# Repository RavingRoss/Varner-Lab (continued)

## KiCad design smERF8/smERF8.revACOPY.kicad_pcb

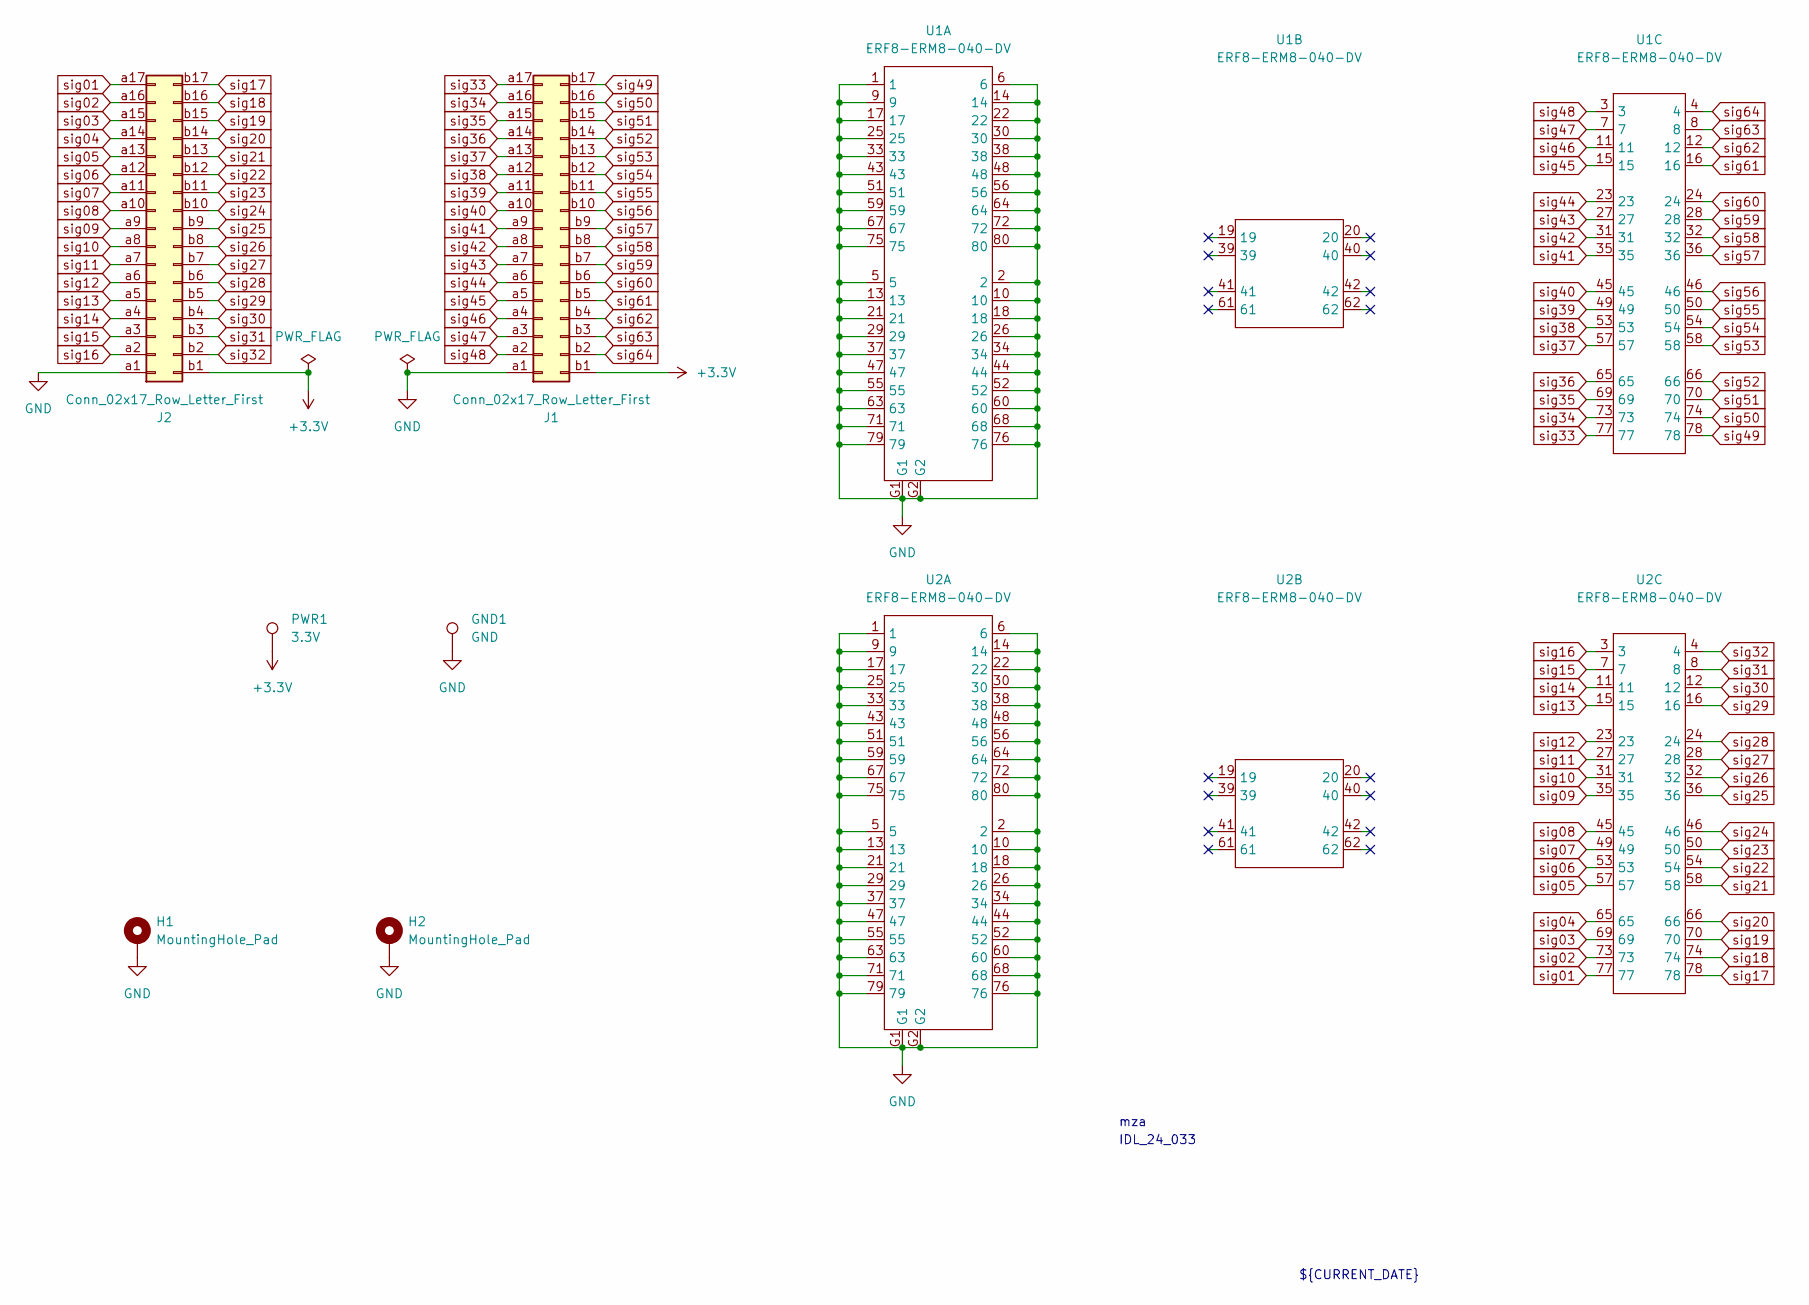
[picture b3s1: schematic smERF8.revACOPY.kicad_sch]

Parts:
GND1: GND; TestPoint_16AWG
H1, H2: MountingHole_Pad; MountingHole_2.7mm_M2.5_Pad
J1, J2: Conn_02x17_Row_Letter_First; 2x17
PWR1: 3.3V; TestPoint_16AWG
U1, U2: ERF8-ERM8-040-DV; erf8-040-dv

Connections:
+3.3V: J1.b1, J2.b1, PWR1.1
GND: GND1.1, H1.1, H2.1, J1.a1, J2.a1, U1.1, U1.2, U1.5, U1.6, U1.9, U1.10, U1.13, U1.14, U1.17, U1.18, U1.21, U1.22, U1.25, U1.26, U1.29, U1.30, U1.33, U1.34, U1.37, U1.38, U1.43, U1.44, U1.47, U1.48, U1.51, U1.52, U1.55, U1.56, U1.59, U1.60, U1.63, U1.64, U1.67, U1.68, U1.71, U1.72, U1.75, U1.76, U1.79, U1.80, U1.G1, U1.G2, U2.1, U2.2, U2.5, U2.6, U2.9, U2.10, U2.13, U2.14, U2.17, U2.18, U2.21, U2.22, U2.25, U2.26, U2.29, U2.30, U2.33, U2.34, U2.37, U2.38, U2.43, U2.44, U2.47, U2.48, U2.51, U2.52, U2.55, U2.56, U2.59, U2.60, U2.63, U2.64, U2.67, U2.68, U2.71, U2.72, U2.75, U2.76, U2.79, U2.80, U2.G1, U2.G2
sig01: J2.a17, U2.77
sig02: J2.a16, U2.73
sig03: J2.a15, U2.69
sig04: J2.a14, U2.65
sig05: J2.a13, U2.57
sig06: J2.a12, U2.53
sig07: J2.a11, U2.49
sig08: J2.a10, U2.45
sig09: J2.a9, U2.35
sig10: J2.a8, U2.31
sig11: J2.a7, U2.27
sig12: J2.a6, U2.23
sig13: J2.a5, U2.15
sig14: J2.a4, U2.11
sig15: J2.a3, U2.7
sig16: J2.a2, U2.3
sig17: J2.b17, U2.78
sig18: J2.b16, U2.74
sig19: J2.b15, U2.70
sig20: J2.b14, U2.66
sig21: J2.b13, U2.58
sig22: J2.b12, U2.54
sig23: J2.b11, U2.50
sig24: J2.b10, U2.46
sig25: J2.b9, U2.36
sig26: J2.b8, U2.32
sig27: J2.b7, U2.28
sig28: J2.b6, U2.24
sig29: J2.b5, U2.16
sig30: J2.b4, U2.12
sig31: J2.b3, U2.8
sig32: J2.b2, U2.4
sig33: J1.a17, U1.77
sig34: J1.a16, U1.73
sig35: J1.a15, U1.69
sig36: J1.a14, U1.65
sig37: J1.a13, U1.57
sig38: J1.a12, U1.53
sig39: J1.a11, U1.49
sig40: J1.a10, U1.45
sig41: J1.a9, U1.35
sig42: J1.a8, U1.31
sig43: J1.a7, U1.27
sig44: J1.a6, U1.23
sig45: J1.a5, U1.15
sig46: J1.a4, U1.11
sig47: J1.a3, U1.7
sig48: J1.a2, U1.3
sig49: J1.b17, U1.78
sig50: J1.b16, U1.74
sig51: J1.b15, U1.70
sig52: J1.b14, U1.66
sig53: J1.b13, U1.58
sig54: J1.b12, U1.54
sig55: J1.b11, U1.50
sig56: J1.b10, U1.46
sig57: J1.b9, U1.36
sig58: J1.b8, U1.32
sig59: J1.b7, U1.28
sig60: J1.b6, U1.24
sig61: J1.b5, U1.16
sig62: J1.b4, U1.12
sig63: J1.b3, U1.8
sig64: J1.b2, U1.4

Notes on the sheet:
mza
IDL_24_033
${CURRENT_DATE}

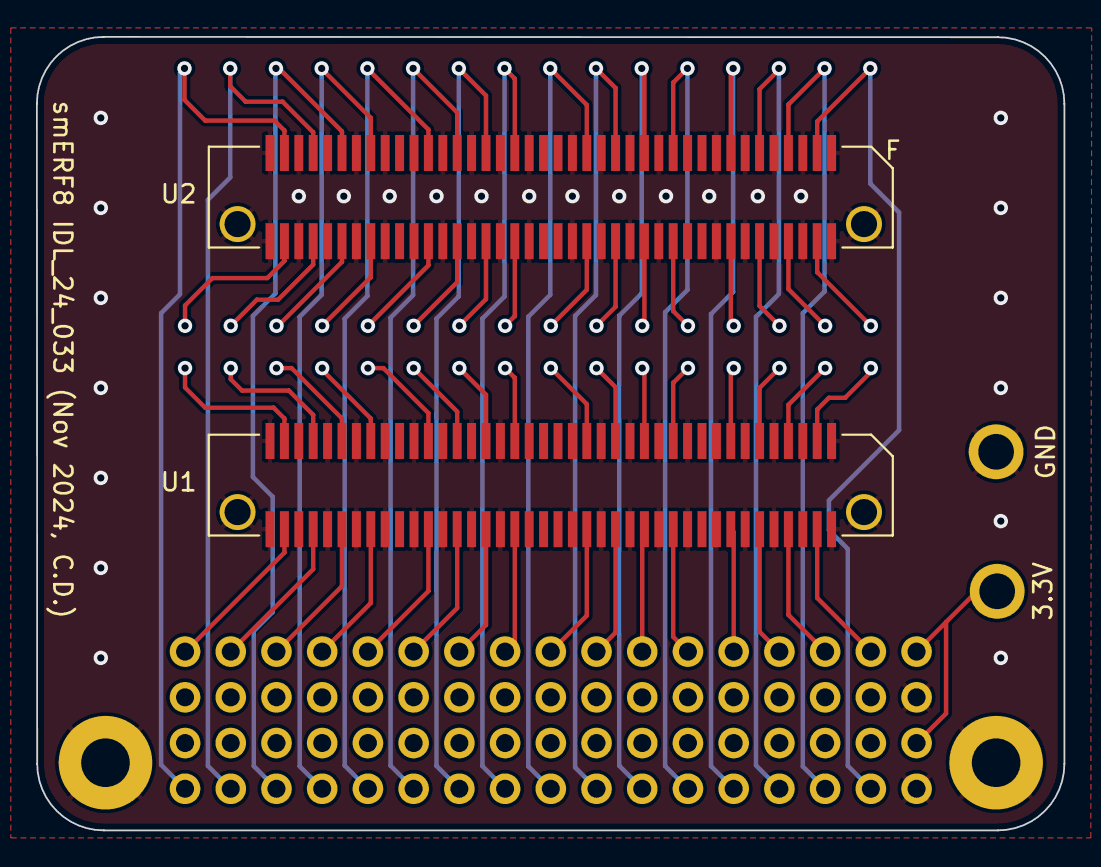
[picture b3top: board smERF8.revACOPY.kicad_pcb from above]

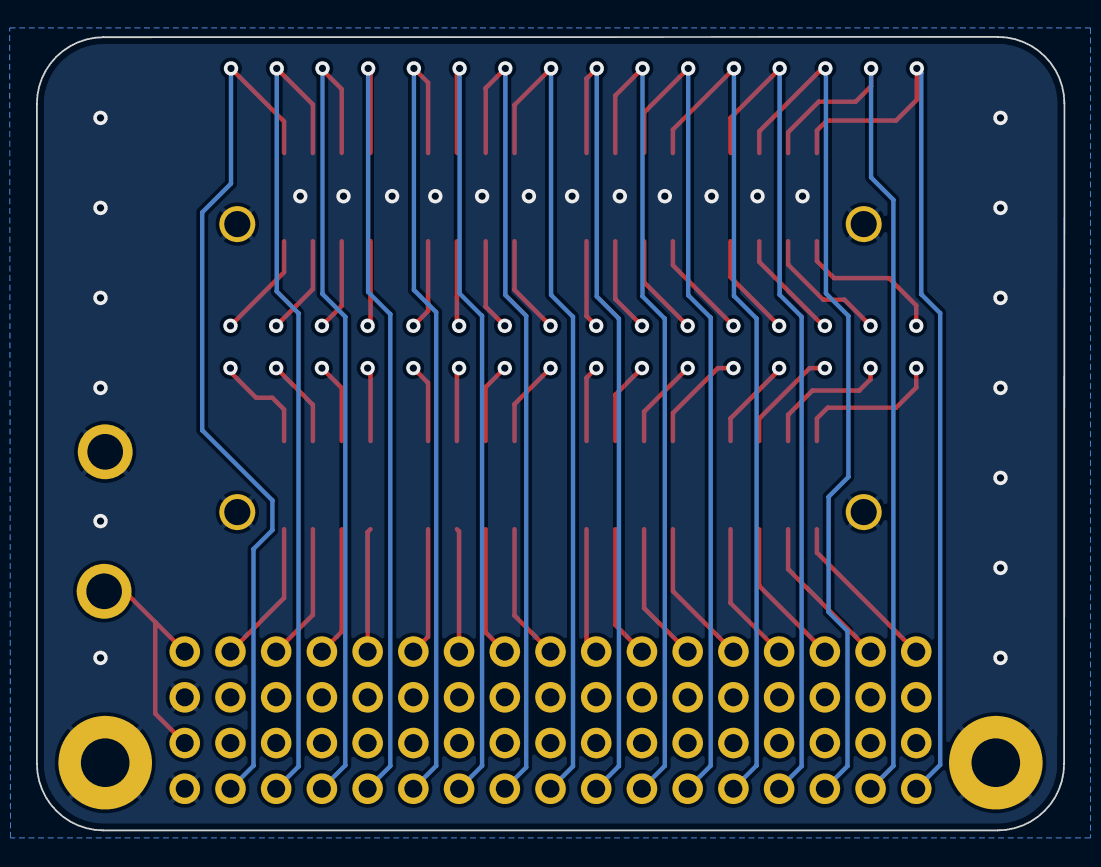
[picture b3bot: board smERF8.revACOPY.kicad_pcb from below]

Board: 4 copper layers, 57.1 x 44.1 mm, 8 parts (2 on the bottom side), 66 nets.

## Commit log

2024-10-22 Initial commit for SiPMT revA
2024-10-22 made gerber files
2024-10-29 Updated the layers and resistors
2024-10-29 updated gerber files
2024-11-25 updated name
2024-11-26 Create smERF8
2024-11-26 Create test
2024-11-26 Add files via upload
    Gerber files
2025-01-30 added waveform ROOT data and python code
2025-04-28 Added RevB and removed 3/4 caps at HV and added 4 caps in Q4 for filtering
2025-05-12 Adding hls4ml project with LFS
2025-05-13 Updated simple keras model
2025-05-13 Adding hls model for vitis-hls
2025-05-13 Updated Keras Model
2025-05-13 updated hls model
2025-05-13 ugh......
2025-05-13 ugh..plz
2025-05-13 ugh..plz...
2025-05-15 Added simulated input data
2025-05-15 Updated simulated data
2025-05-15 Added vitis-hls synt, vivado project, and vivado sim results
2025-05-15 added final report
2025-05-29 Added XRM for parallels session
2025-05-29 updated XRM files
2025-06-04 Added hls4ml
2025-09-22 Made pcie40-waveforms script, updated TOP-BS
2025-09-23 Added fusion files for cooling plate
2025-11-16 Pushing new code update with images and logs along with initial commit of LED Distribution PCB
2025-11-16 Deleted large file, did not need it anyways (I think)
2025-11-27 Updated Distribution PCB sch
